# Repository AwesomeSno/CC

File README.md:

# MEMENTO (CC)

An intelligent personal memory and conversation analysis device built for Hack Club's Half Life. MEMENTO captures authorized real-world conversations on a dedicated, portable hardware recorder, preserves them to local microSD storage, and syncs with a local macOS companion app for on-device transcription, speaker diarization, vocal tone analysis, and daily executive summaries.

---

## What is this?

Most voice recorders and note-taking apps on the market are completely passive: they record hours of audio into a dead folder of giant audio files that you never listen to again, or dump them into a third-party cloud that turns spoken human nuance into flat, robotic text blocks.

**MEMENTO** is a personal memory infrastructure. It combines a dedicated hardware pendant recorder with a local-first desktop intelligence pipeline:

1. **Hardware Capture Unit (MEMENTO ONE)**: A featherweight 75mm × 42mm × 15mm clip-on device powered by an ESP32-S3 and high-SNR INMP441 I2S digital MEMS microphone. It records uncompressed 16kHz 16-bit PCM audio directly to a 32GB microSD card with a hardware mute switch, 0.96" OLED status screen, and silent haptic motor.
2. **Local AI Desktop Engine (Mac)**: Ingests audio sessions over USB-C or local Wi-Fi, performs word-level timestamped transcription (`whisper.cpp` / `faster-whisper`), segments speakers (`pyannote.audio`), extracts acoustic features (`librosa` vocal pitch, jitter, pauses), and prompts a local LLM (`ollama`) to produce structured conversation reports.
3. **Interview & Vocal Coaching**: Evaluates conversation dynamics—detecting hesitation, questions missed or evaded, commitments made, listener engagement, and acoustic vocal intensity.
4. **Searchable Daily Memory**: Chronological timeline of your day backed by a local SQLite database with FTS5 full-text search and provenance linking every observation directly to its source audio timestamp.

---

## Hardware Specifications

| Subsystem | Component | Specifications |
| :--- | :--- | :--- |
| **Microcontroller** | ESP32-S3-WROOM-1 | Dual-core Tensilica Xtensa LX7 @ 240MHz, 8MB PSRAM, 8MB Flash |
| **Microphone** | InvenSense INMP441 | I2S digital MEMS, 61 dBA SNR, 24-bit PCM acquisition |
| **Storage** | MicroSD Slot | SPI / SDMMC bus, FAT32 filesystem, 32GB high-endurance card |
| **Display** | 0.96" I2C OLED (SSD1306) | 128×64 resolution, auto-dimming status and battery telemetry |
| **Haptics** | 1027 ERM Coin Motor | AO3400A MOSFET driver for silent tactile notifications |
| **Power & Battery** | 1200mAh 3.7V LiPo | TP4056 linear charger, ME6211 3.3V ultra-low-noise LDO, USB-C |
| **Controls** | Hardware Switches | Physical slide mute switch, tactile record button, bookmark button |
| **Dimensions** | 75mm × 42mm × 15mm | 3D-printed PETG enclosure with spring clip and acoustic funnel |

---

## Repository Structure

```
CC/
├── README.md               # Engineering specification and project reference
├── JOURNAL.md              # Mirrored devlog formatted for Half Life sync
├── BOM.csv                 # Detailed Bill of Materials ($33 hardware subtotal)
├── SHOPPING_LIST.md        # Procurement links and component allowances
├── journal/                # Conversational devlog entries
│   ├── first_5_hours.md    # First 5 hours: Architecture, I2S mic & power tree
│   ├── hours_5_to_10.md    # Hours 5-10: Hardware privacy, local AI, CAD & BOM check
│   ├── next_15_hours.md    # Hours 11-25: KiCad schematic, PCB layout & CAD
│   ├── hours_25_to_35.md   # Hours 25-35: Desktop intelligence & interview coach
│   └── images/             # 1200x800 engineering sketches and diagrams
├── kicad/                  # Complete KiCad 10 hardware project
│   ├── memento.kicad_pro   # KiCad project file
│   ├── memento.kicad_sch   # Full multi-sheet schematic
│   ├── memento.kicad_pcb   # 2-layer routed PCB with isolated audio zone
│   ├── memento_schematic.pdf
│   ├── memento_gerbers.zip # JLCPCB production files
│   └── renders/            # 3D PCB raytraced renders
├── cad/                    # 3D CAD models
│   ├── 01_front_housing.scad
│   ├── 02_rear_clip_housing.scad
│   ├── 03_button_actuators.scad
│   └── memento_assembly.scad
├── firmware/               # ESP-IDF FreeRTOS C++ firmware
│   ├── main/               # Main application and task orchestration
│   └── components/         # Modular drivers (audio, storage, display, power)
├── desktop/                # Local macOS AI intelligence pipeline
│   ├── pipeline/           # Ingestion, Whisper transcription, PyAnnote, Librosa
│   ├── database/           # SQLite schema and FTS5 search
│   └── run_memento.py      # Local CLI and dashboard server
├── video-scripts/          # Production reel scripts with timed visual breakdowns
│   ├── idea_reel_script.md # Project idea & kickoff reel (~42s)
│   ├── script_5h.md        # 5-hour architecture reel
│   ├── script_15h.md       # 15-hour hardware & KiCad reel
│   ├── script_35h.md       # 35-hour local AI intelligence reel
│   └── final_showcase_script.md # Final product walkthrough
├── Videos/                 # Generated video assets, voiceovers, and subtitles
│   ├── memento_idea_reel.mp4
│   ├── memento_5h_progress_reel.mp4
│   ├── memento_15h_progress_reel.mp4
│   ├── memento_35h_progress_reel.mp4
│   └── memento_final_showcase_reel.mp4
└── scripts/
    └── journal.py          # Devlog verification and image link checker
```

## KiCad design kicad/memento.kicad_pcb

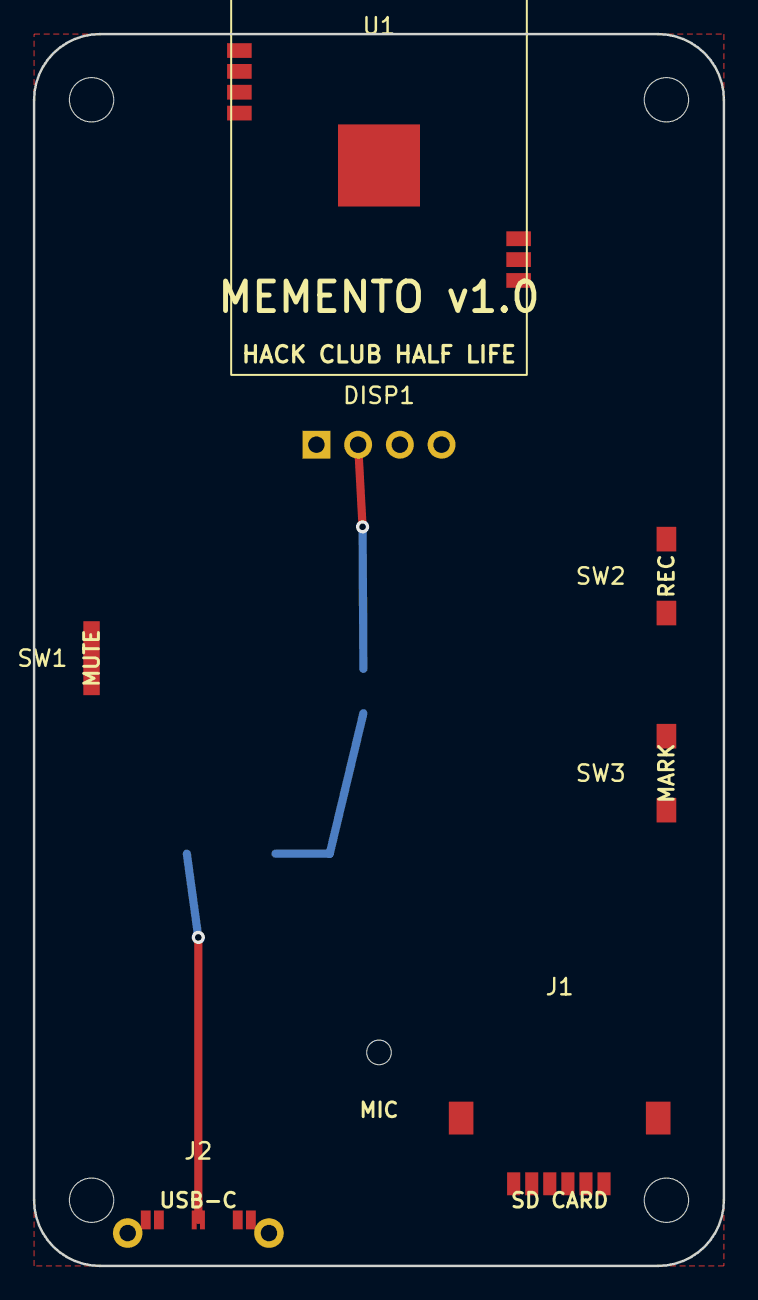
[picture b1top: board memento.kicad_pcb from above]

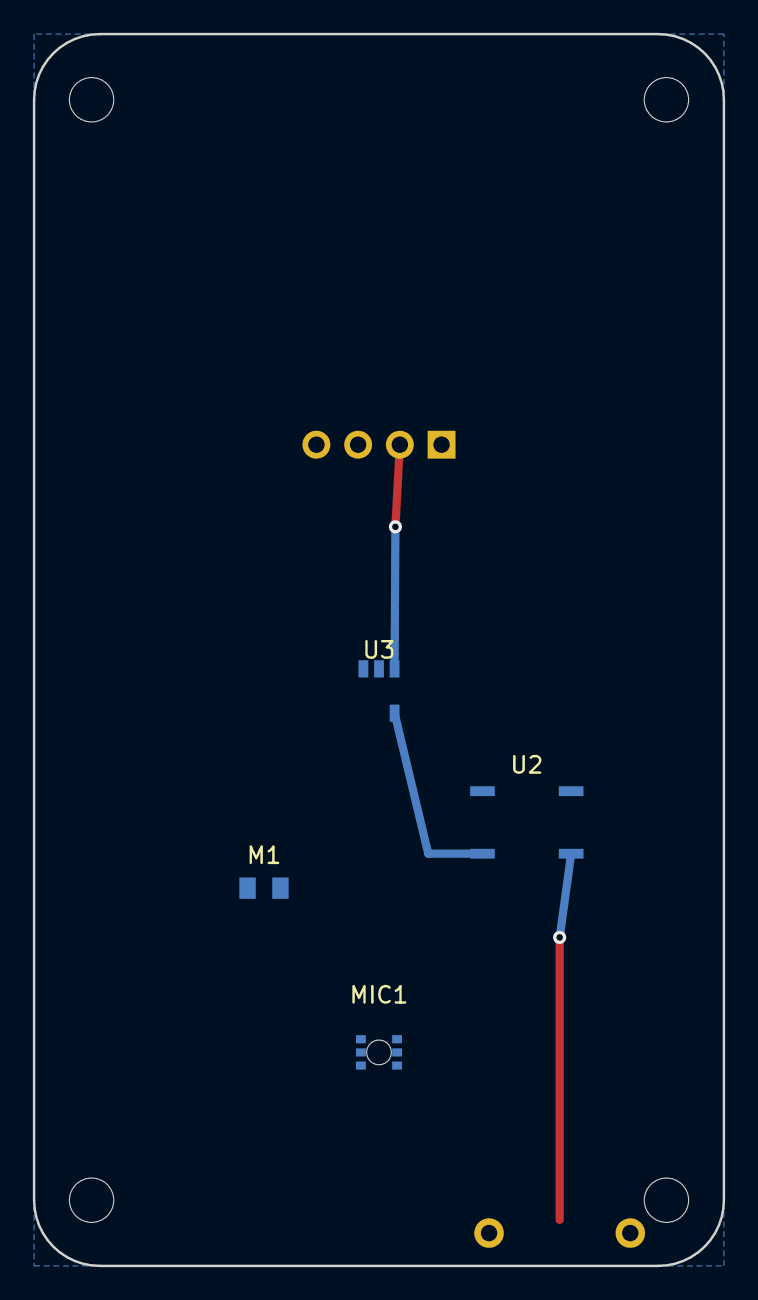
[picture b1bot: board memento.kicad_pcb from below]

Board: 2 copper layers, 42.0 x 75.0 mm, 11 parts (4 on the bottom side), 7 nets.

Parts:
DISP1: OLED_0.96_SSD1306; PinHeader_1x04_P2.54mm_Vertical
J1: MicroSD_Socket; microSD_HC_Hirose_DM3AT-SF-PEJM5
J2: USB_C_16P; USB_C_Receptacle_HRO_TYPE-C-31-M-12
M1: 1027_ERM_MOTOR; R_0805_2012Metric
MIC1: INMP441; InvenSense_INMP441
SW1: SPDT_MUTE; SW_SPDT_CK_JS102011SAQN
SW2: BTN_REC; SW_Push_1P1T_NO_6x6mm_H9.5mm
SW3: BTN_MARK; SW_Push_1P1T_NO_6x6mm_H9.5mm
U1: ESP32-S3-WROOM-1-N8R8; ESP32-S3-WROOM-1
U2: TP4056; SOIC-8_3.9x4.9mm_P1.27mm
U3: ME6211C33M5G; SOT-23-5

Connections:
+3V3: DISP1.2, J1.4, SW1.1, U1.2, U3.5
GND: DISP1.1, J1.6, J1.SH1, J1.SH2, J2.A1, J2.B1, J2.SH1, J2.SH2, MIC1.4, MIC1.5, SW1.3, SW2.2, SW3.2, U1.1, U1.19, U1.41, U2.1, U3.2
MIC_VDD: MIC1.6, SW1.2
USB_D_N: J2.A7, U1.20
USB_D_P: J2.A6, U1.21
VBAT: M1.1, U2.5, U3.1, U3.3
VBUS_5V: J2.A4, J2.B4, U2.4, U2.8
